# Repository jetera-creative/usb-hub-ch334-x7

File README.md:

# usb-hub-ch334-x7
USB 2.0 Hub powered by CH334R with 7 ports.

## Features

### Supported connectors

- USB Micro-B
- USB Type-C

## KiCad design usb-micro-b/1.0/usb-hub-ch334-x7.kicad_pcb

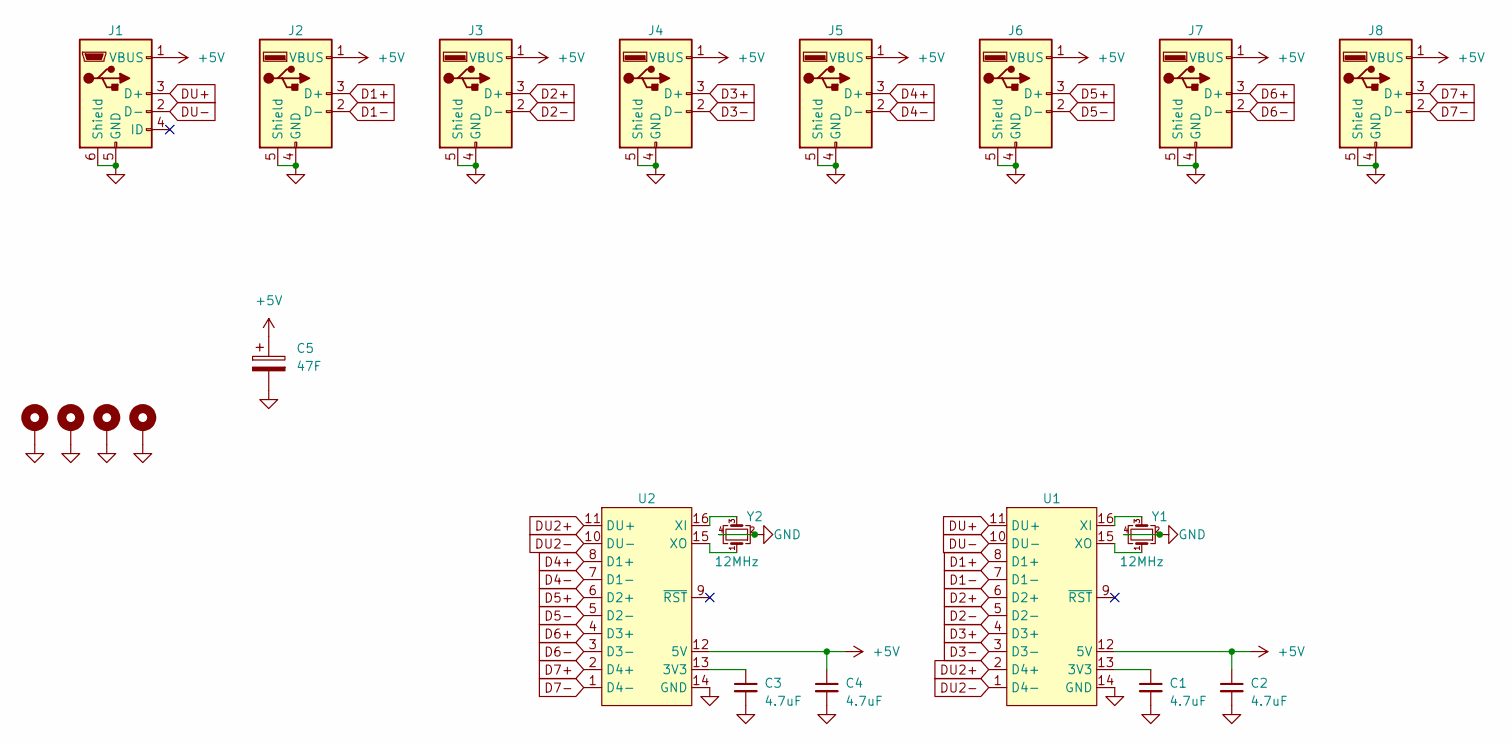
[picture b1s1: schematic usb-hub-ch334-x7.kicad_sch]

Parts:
C1, C2, C3, C4: 4.7uF; C_0805_2012Metric
C5: 47F; CP_Radial_D18.0mm_P7.50mm
H1, H2, H3, H4: MountingHole_Pad; MountingHole_2.5mm_Pad_Via
J1: USB_B_Micro; USB_Micro-B_Wuerth_629105150521
J2, J3, J4, J5, J6, J7, J8: USB_A; USB_A_Stewart_SS-52100-001_Horizontal
U1, U2: CH334R; QSOP-16_3.9x4.9mm_P0.635mm
Y1, Y2: 12MHz; Crystal_SMD_3225-4Pin_3.2x2.5mm

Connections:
+5V: C2.1, C4.1, C5.1, J1.1 (VBUS), J2.1 (VBUS), J3.1 (VBUS), J4.1 (VBUS), J5.1 (VBUS), J6.1 (VBUS), J7.1 (VBUS), J8.1 (VBUS), U1.12 (5V), U2.12 (5V)
D1+: J2.3 (D+), U1.8 (D1+)
D1-: J2.2 (D-), U1.7 (D1-)
D2+: J3.3 (D+), U1.6 (D2+)
D2-: J3.2 (D-), U1.5 (D2-)
D3+: J4.3 (D+), U1.4 (D3+)
D3-: J4.2 (D-), U1.3 (D3-)
D4+: J5.3 (D+), U2.8 (D1+)
D4-: J5.2 (D-), U2.7 (D1-)
D5+: J6.3 (D+), U2.6 (D2+)
D5-: J6.2 (D-), U2.5 (D2-)
D6+: J7.3 (D+), U2.4 (D3+)
D6-: J7.2 (D-), U2.3 (D3-)
D7+: J8.3 (D+), U2.2 (D4+)
D7-: J8.2 (D-), U2.1 (D4-)
DU2+: U1.2 (D4+), U2.11 (DU+)
DU2-: U1.1 (D4-), U2.10 (DU-)
DU+: J1.3 (D+), U1.11 (DU+)
DU-: J1.2 (D-), U1.10 (DU-)
GND: C1.2, C2.2, C3.2, C4.2, C5.2, H1.1, H2.1, H3.1, H4.1, J1.5 (GND), J1.6 (Shield), J2.4 (GND), J2.5 (Shield), J3.4 (GND), J3.5 (Shield), J4.4 (GND), J4.5 (Shield), J5.4 (GND), J5.5 (Shield), J6.4 (GND), J6.5 (Shield), J7.4 (GND), J7.5 (Shield), J8.4 (GND), J8.5 (Shield), U1.14 (GND), U2.14 (GND), Y1.2, Y1.4, Y2.2, Y2.4
unnamed: C1.1, U1.13 (3V3)
unnamed: U1.16 (XI), Y1.3
unnamed: U1.15 (XO), Y1.1
unnamed: C3.1, U2.13 (3V3)
unnamed: U2.16 (XI), Y2.3
unnamed: U2.15 (XO), Y2.1

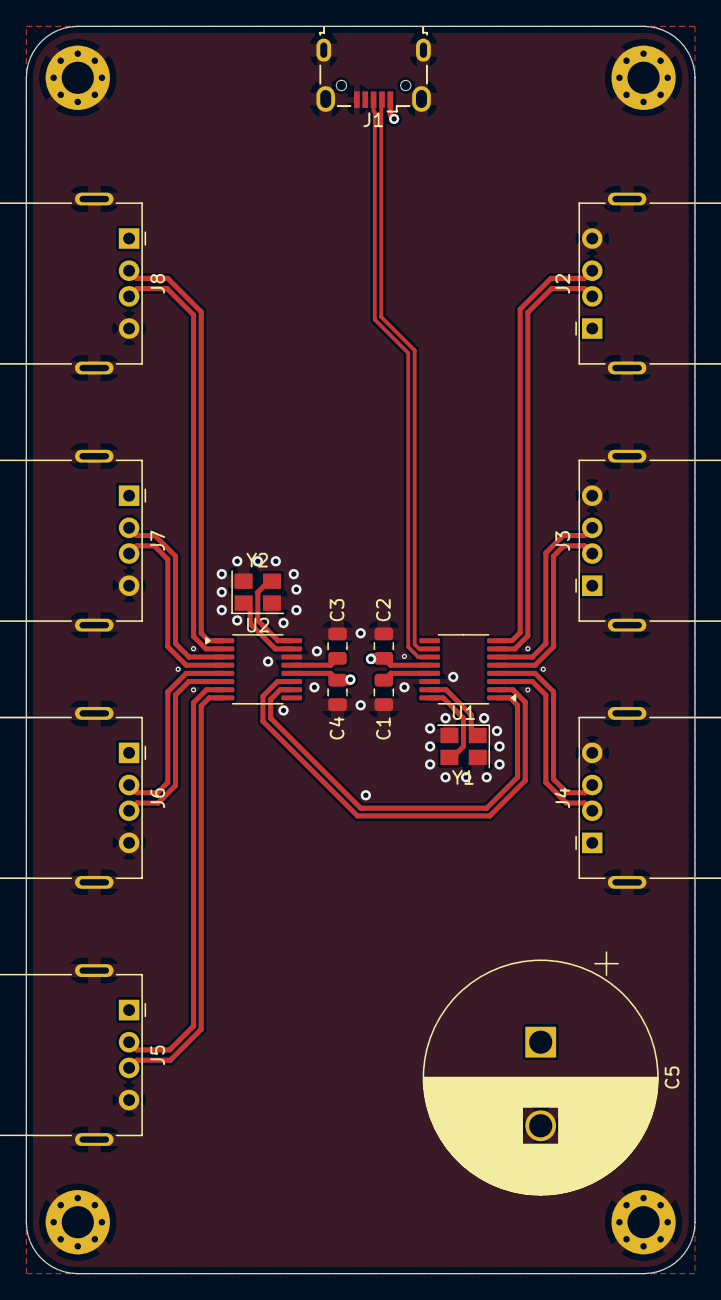
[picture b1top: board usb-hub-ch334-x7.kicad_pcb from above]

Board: 4 copper layers, 52.0 x 97.0 mm, 21 parts (0 on the bottom side), 26 nets.

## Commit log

2024-09-01 Rev 1.0 for Type-C and Micro-B

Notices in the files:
usb-micro-b/1.0/usb-hub-ch334-x7.kicad_pcb:
Copyright © 2024 JetERA Creative
